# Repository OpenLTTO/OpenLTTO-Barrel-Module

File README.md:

# OpenLTTO
The OpenLTTO Project is an attempt to recreate the Lazer Tag Team Ops protocol, and game system, in a completely open-source solution. Eventually our intent, is to expand on the LTTO system, adding new functionality, and features, while maintaining backwards compatibility with this classic Lazer Tag gear.

> This Project wouldn't be possible without all the hard work of Richie Mickan https://github.com/rmick
> His work on recreating the LTTO Protocol, and the development of the Combobulator app are core to the firmware and capabilities of this project.

> Additionally this is built on top of the excellent product developed and released by Hasbro/Tiger Electronics. And the work done by Tag Ferret to release the technical specs, and unlock much of the magic of the protocol, and the inner workings.

We intend to do this via a collection of open-source hardware components that can act as building blocks, to build anything you might require for a Lazer Tag game (Taggers, Hosting Pods, Zone controllers, utilities, etc). And an opensource firmware to operate it all. 

Shield: [![CC BY-NC-SA 4.0][cc-by-nc-sa-shield]][cc-by-nc-sa]

This work is licensed under a
[Creative Commons Attribution-NonCommercial-ShareAlike 4.0 International License][cc-by-nc-sa].

[![CC BY-NC-SA 4.0][cc-by-nc-sa-image]][cc-by-nc-sa]

[cc-by-nc-sa]: http://creativecommons.org/licenses/by-nc-sa/4.0/
[cc-by-nc-sa-image]: https://licensebuttons.net/l/by-nc-sa/4.0/88x31.png
[cc-by-nc-sa-shield]: https://img.shields.io/badge/License-CC%20BY--NC--SA%204.0-lightgrey.svg

# OpenLTTO Barrel Module
The OpenLTTO Barrel Module is designed to mimic the form factor of the LTTO Deluxe blasters "Dual Barrel" Setup, with one optical tube being transmit, and one optical tube for receive. It is designed to easily fit in the end of a 3D Printed optical tube, with a 25mm focusing lens. 

The module includes 5 Pin IR IN and IR OUT ports, as well as an optimized 1A LED Driver for the IR LED, along with paired Muzzle Flash LEDs. The Module supports both outdoor (high power, 1A), and indoor (low power) modes, controlled from the motherboard. And includes a power ballast (capacitor, and inrush arrester pair) to prevent ripples, and ensure smooth operation.

## OpenLTTO Barrel Module Front Side

## OpenLTTO Barrel Module Back Side

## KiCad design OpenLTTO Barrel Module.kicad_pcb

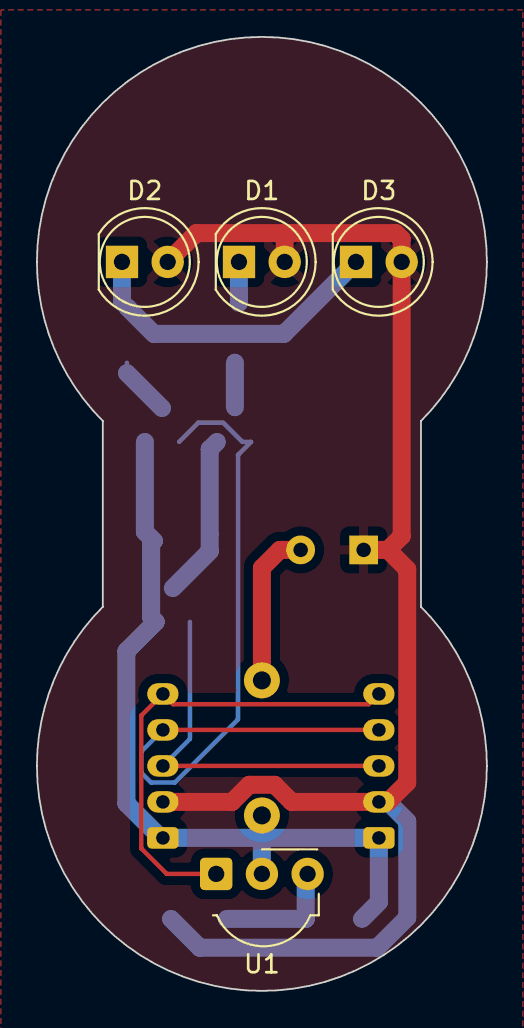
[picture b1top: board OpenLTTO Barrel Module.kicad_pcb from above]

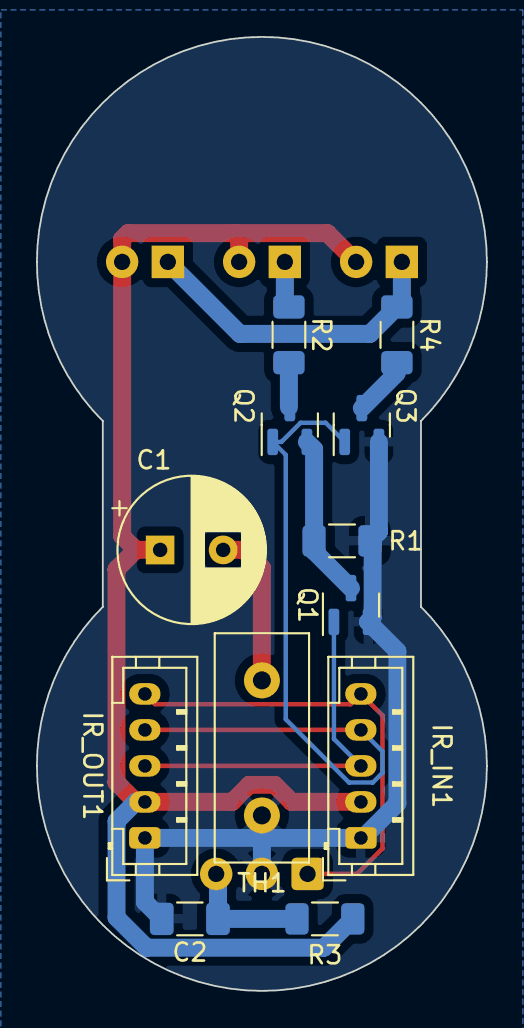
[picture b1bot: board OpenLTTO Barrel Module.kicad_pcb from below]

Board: 2 copper layers, 25.0 x 53.0 mm, 16 parts (12 on the bottom side), 12 nets.

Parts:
C1: 560uf; CP_Radial_D8.0mm_P3.50mm
C2: 0.1uf; C_1206_3216Metric_Pad1.33x1.80mm_HandSolder
D1: TSAL6100; LED_D5.0mm_IRBlack
D2, D3: LED; LED_D5.0mm_Clear
IR_IN1: JST_PH_B5B-PH-K_1x05_P2.00mm_Vertical
IR_OUT1: JST_PH_B5B-PH-K_1x05_P2.00mm_Vertical
Q1, Q2, Q3: IRLML6244; SOT-23
R1, R4: 51; R_1206_3216Metric_Pad1.30x1.75mm_HandSolder
R2: 3.3; R_1206_3216Metric_Pad1.30x1.75mm_HandSolder
R3: 100; R_1206_3216Metric_Pad1.30x1.75mm_HandSolder
TH1: MF72-050D9; C_Disc_D12.5mm_W5.0mm_P7.50mm
U1: TSOP4138; Vishay_MOLD-3Pin

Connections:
+5V: C1.1, D1.2 (A), D2.2 (A), D3.2 (A), IR_IN1.2, IR_OUT1.2, R3.2
/IR_MODE: IR_IN1.3, IR_OUT1.3, Q1.1 (G)
/IR_RX: IR_IN1.5, IR_OUT1.5, U1.1 (OUT)
/IR_TX: IR_IN1.4, IR_OUT1.4, Q2.1 (G), Q3.1 (G)
GND: C2.2, IR_IN1.1, IR_OUT1.1, Q1.2 (S), Q3.2 (S), R1.2, TH1.2, U1.2 (GND)
unnamed: C1.2, TH1.1
unnamed: D1.1 (K), R2.1
unnamed: D2.1 (K), D3.1 (K), R4.1
unnamed: Q1.3 (D), Q2.2 (S), R1.1
unnamed: Q2.3 (D), R2.2
unnamed: Q3.3 (D), R4.2
unnamed: C2.1, R3.1, U1.3 (Vs)

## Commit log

2024-02-01 Updated schematic metadata, added schematic PDF and renders of PCB
2024-02-02 Added license and updated readme
2024-02-02 Updated module to allow 3mm gap between optical elements (for easier assembly design)
2024-02-03 Minor change, shifted ballast cap to make room for internal baffle on optical assembly
